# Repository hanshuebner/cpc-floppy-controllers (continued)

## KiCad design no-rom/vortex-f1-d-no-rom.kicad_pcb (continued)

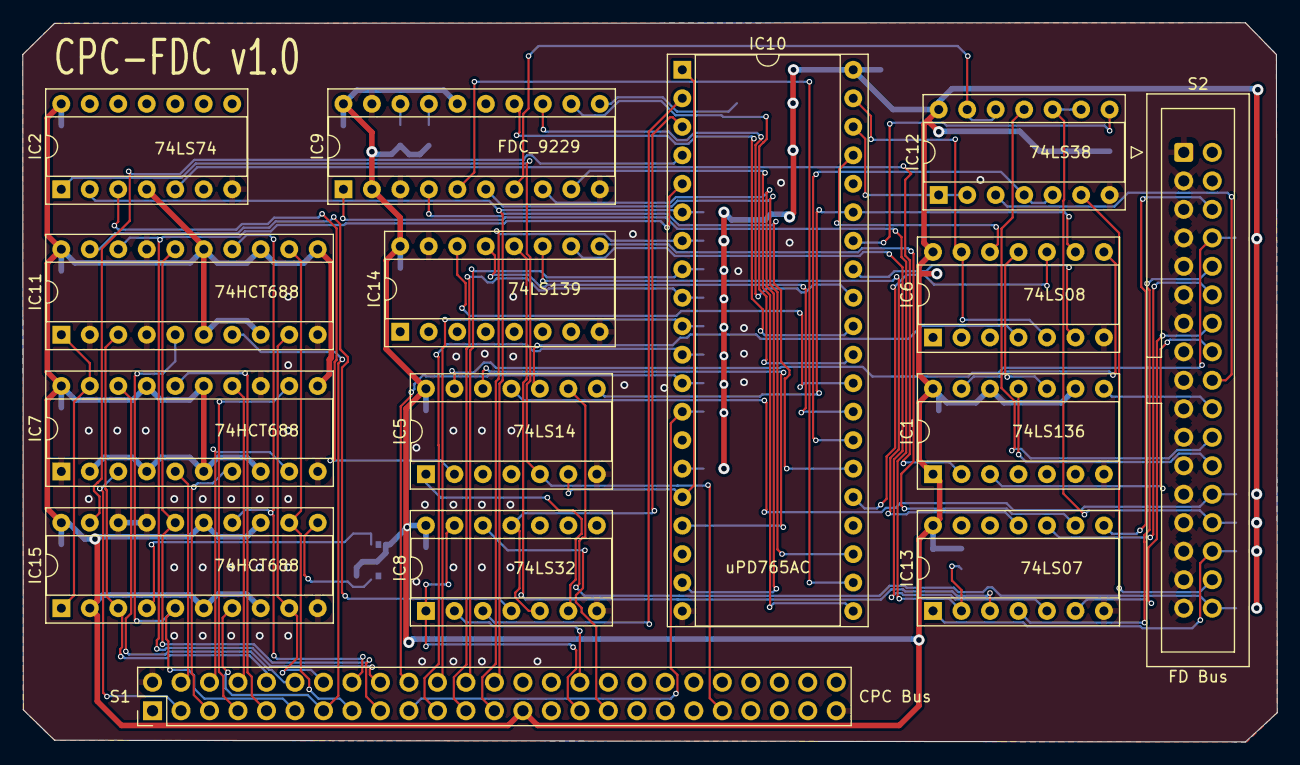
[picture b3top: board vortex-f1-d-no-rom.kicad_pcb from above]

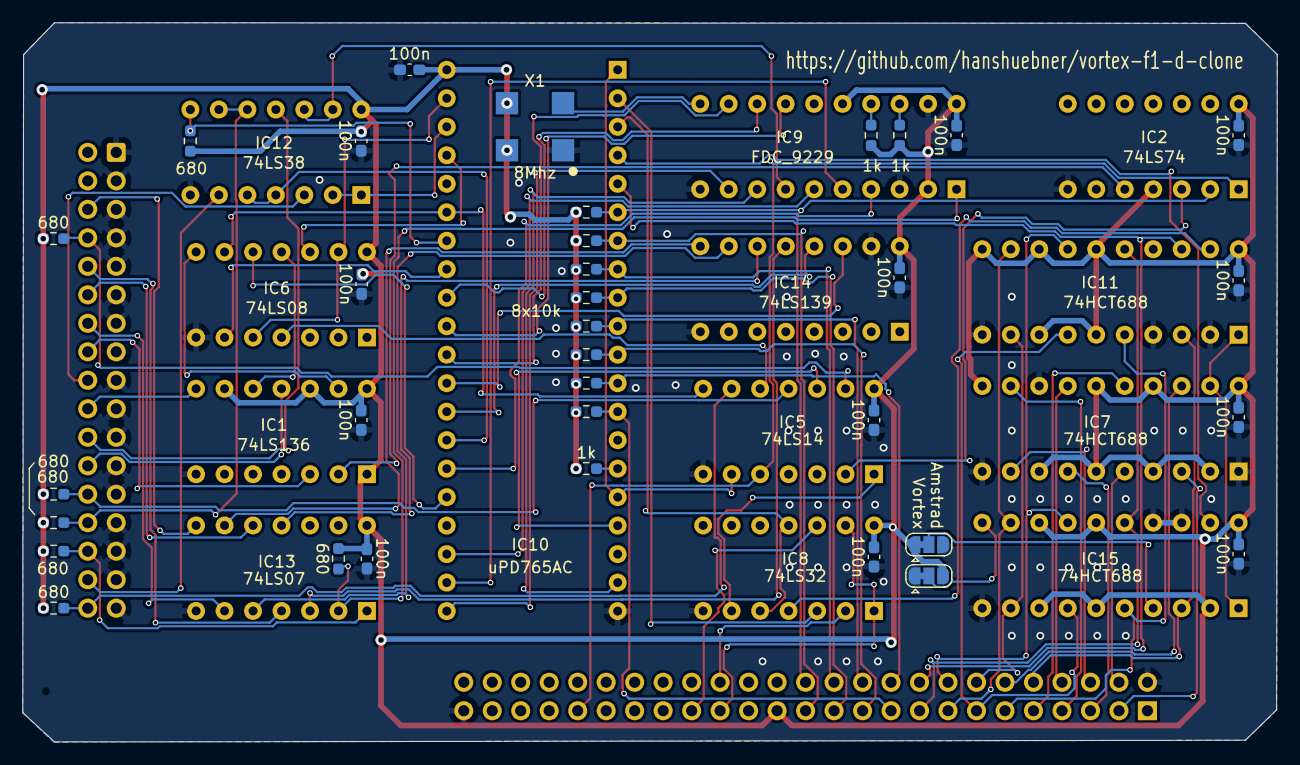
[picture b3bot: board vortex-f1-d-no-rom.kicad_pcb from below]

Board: 2 copper layers, 111.9 x 64.1 mm, 49 parts (34 on the bottom side), 88 nets.

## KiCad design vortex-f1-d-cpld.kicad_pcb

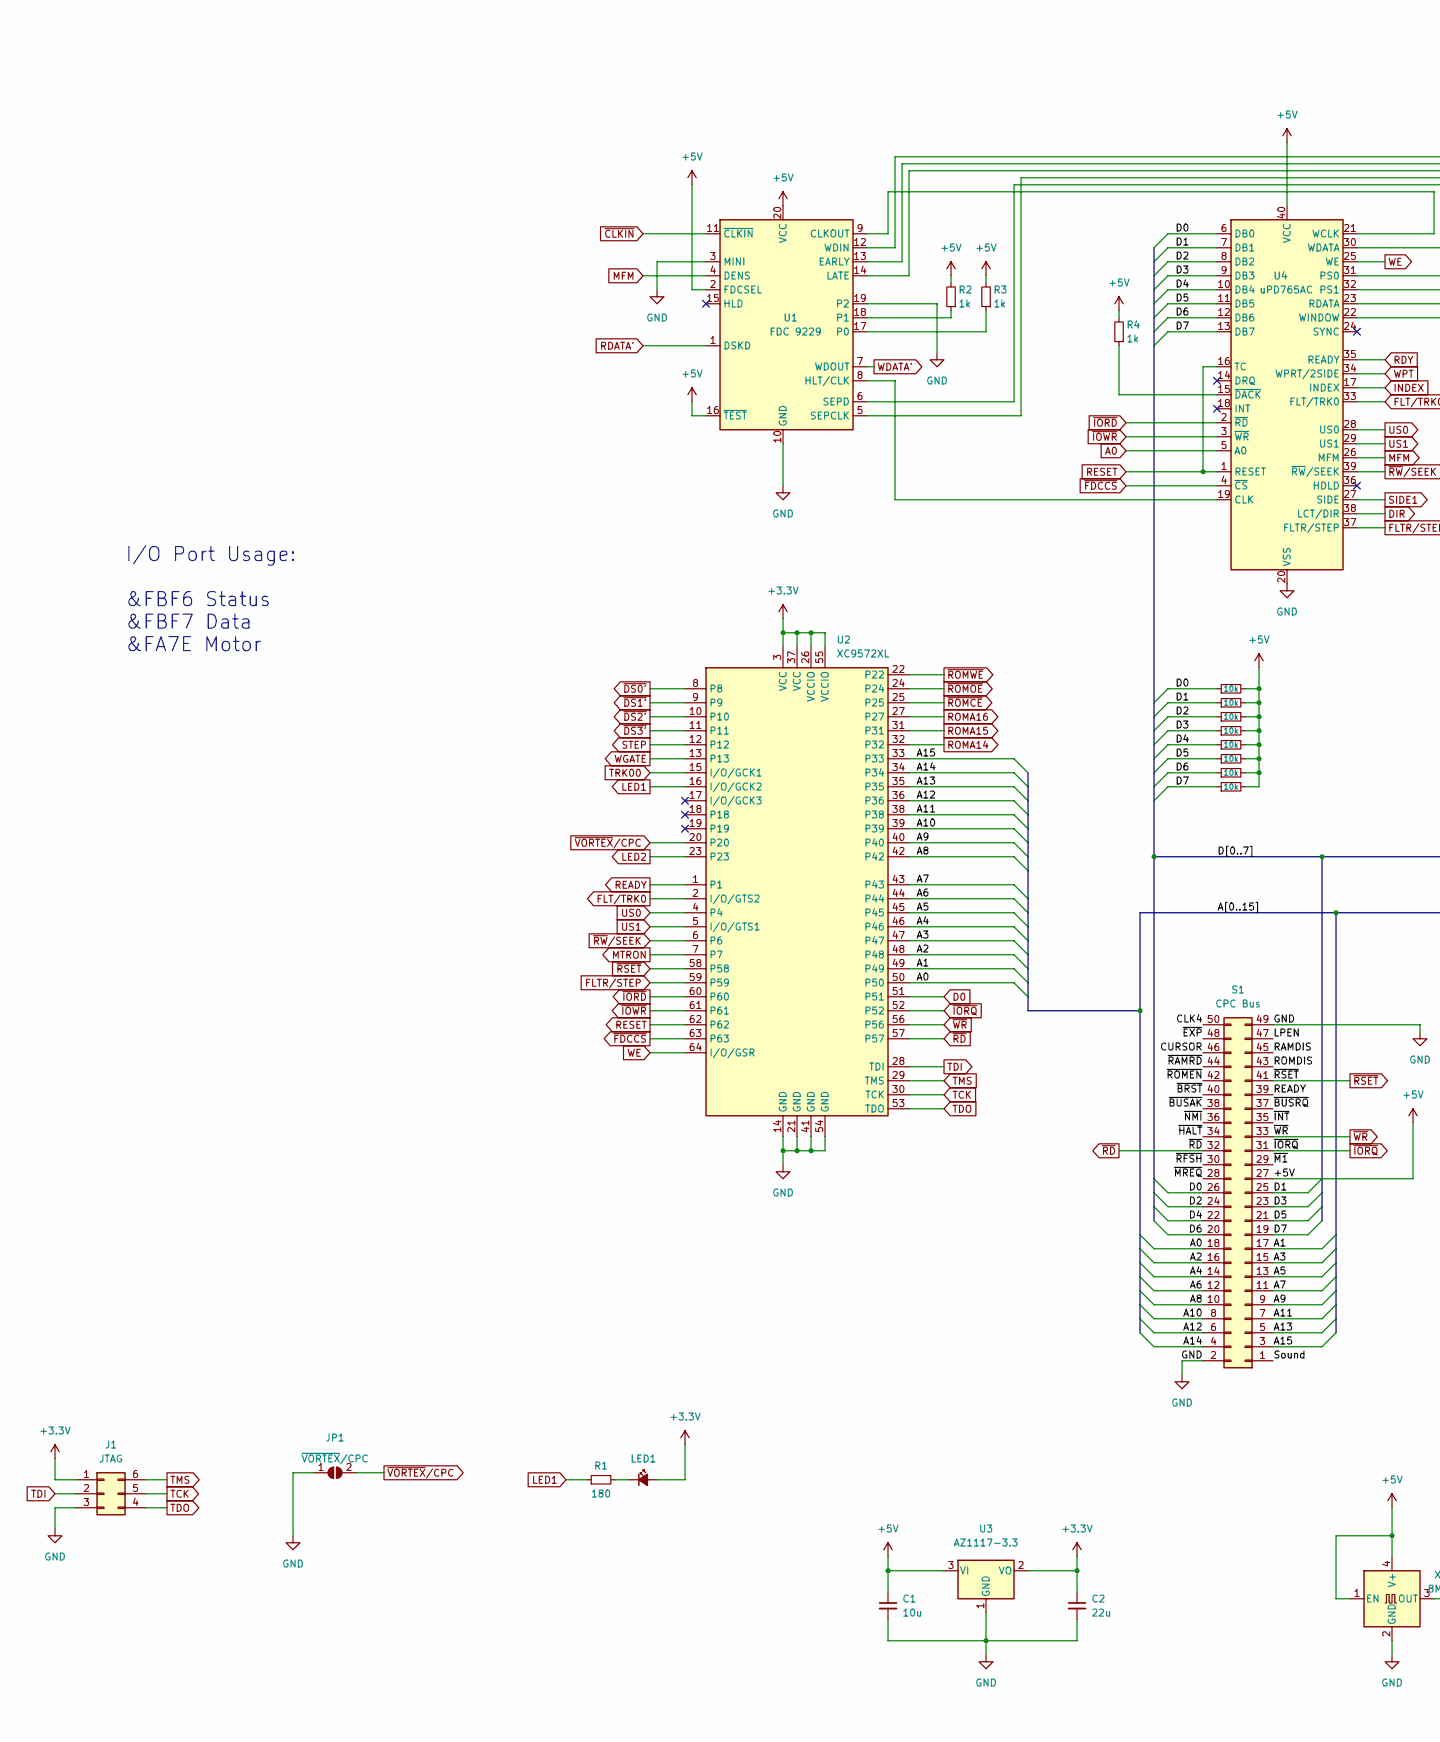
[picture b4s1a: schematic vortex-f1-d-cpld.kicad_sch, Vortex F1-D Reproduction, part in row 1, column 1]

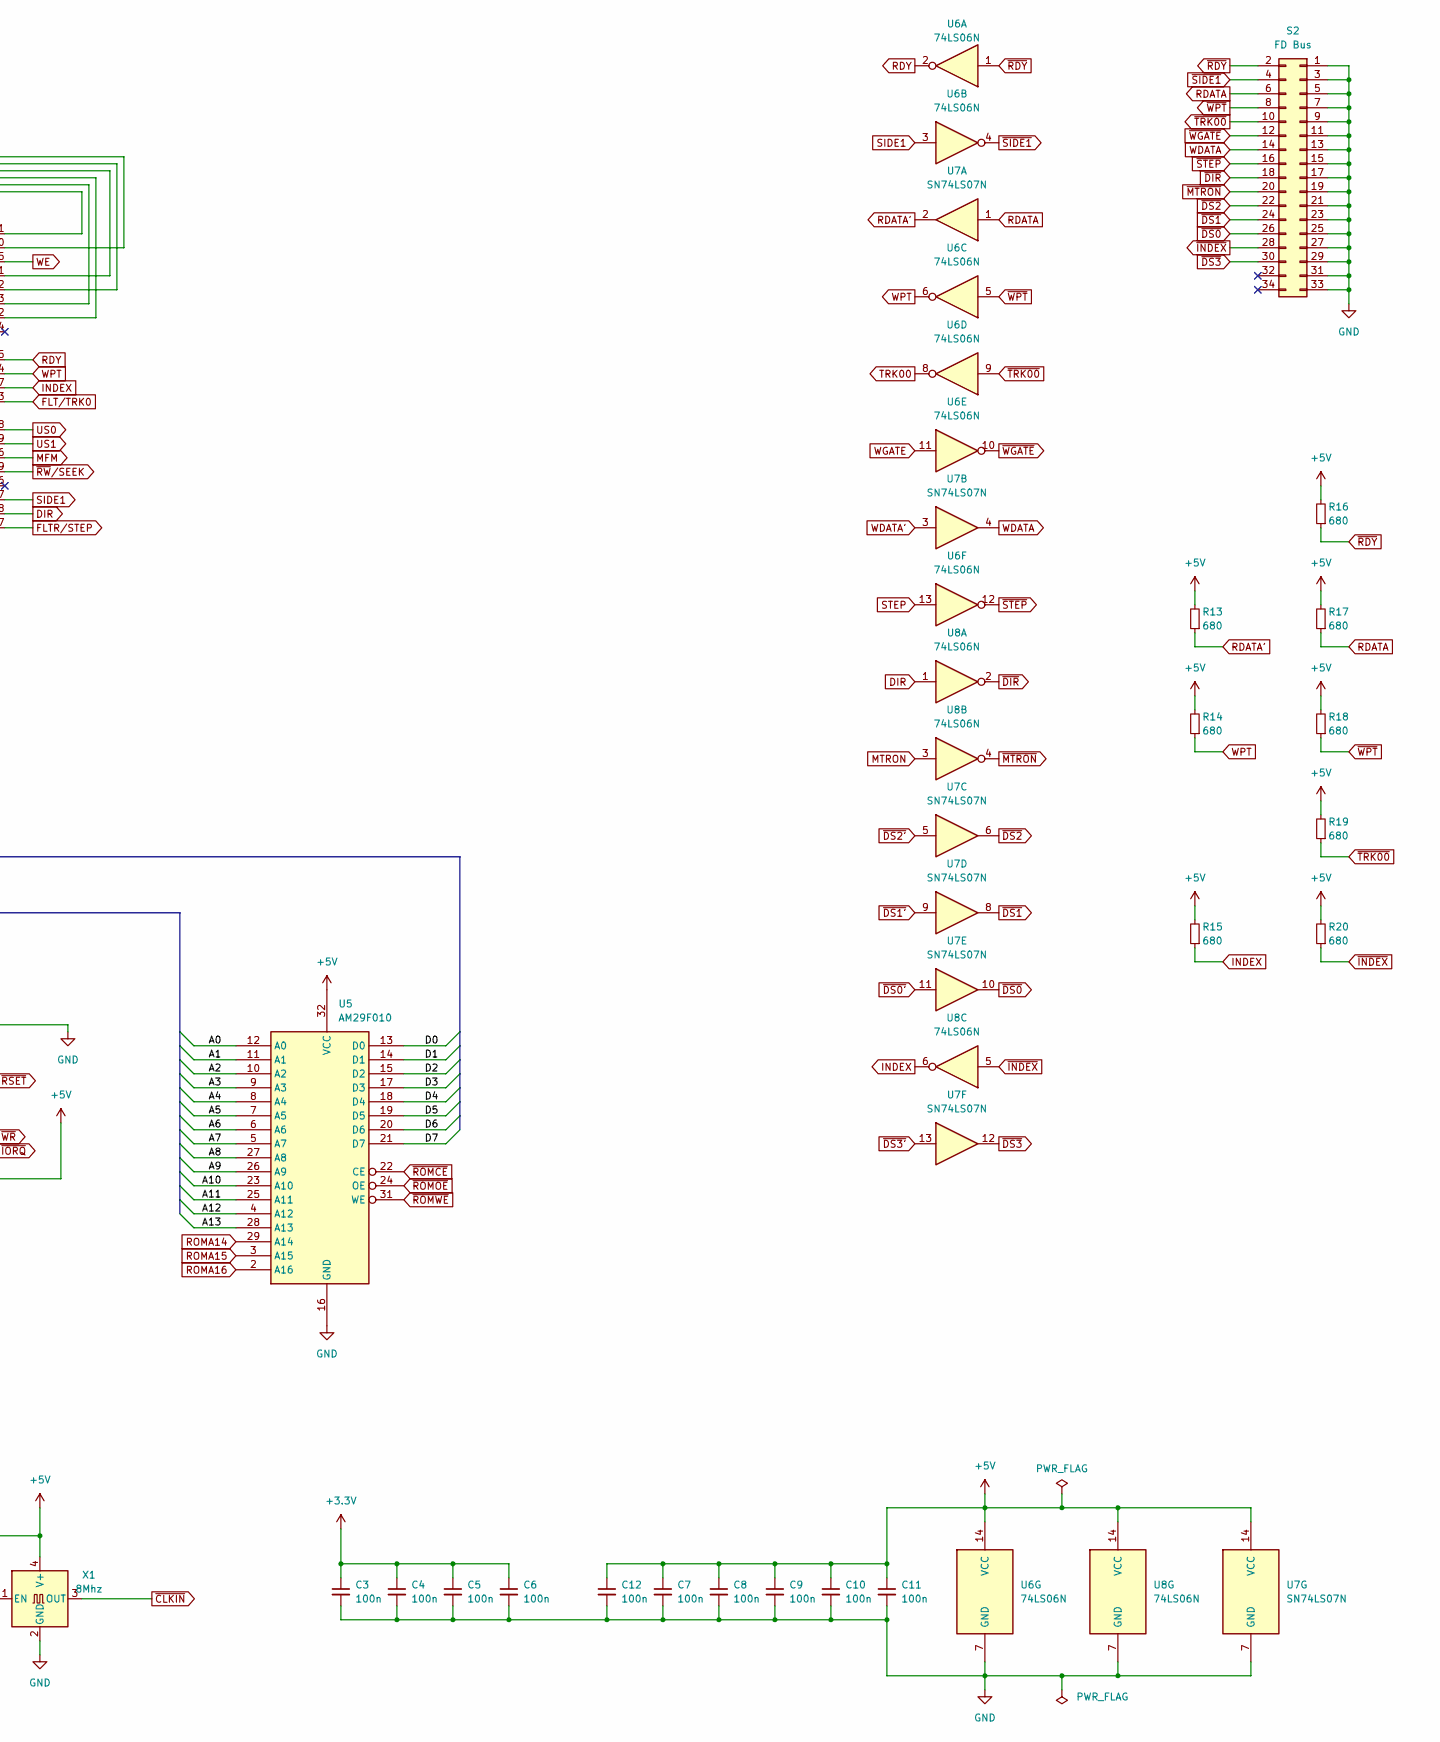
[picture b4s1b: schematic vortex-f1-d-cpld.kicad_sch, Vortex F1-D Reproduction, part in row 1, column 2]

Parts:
C1: 10u; C_0603_1608Metric_Pad1.08x0.95mm_HandSolder
C2: 22u; C_0603_1608Metric_Pad1.08x0.95mm_HandSolder
C3, C4, C5, C6, C7, C8, C9, C10, C11, C12: 100n; C_0603_1608Metric_Pad1.08x0.95mm_HandSolder
J1: JTAG; PinHeader_2x03_P2.54mm_Vertical
JP1: ~{VORTEX}/CPC; SolderJumper-2_P1.3mm_Open_RoundedPad1.0x1.5mm
LED1: STATUS; LED_0805_2012Metric_Pad1.15x1.40mm_HandSolder
R1: 180; R_0603_1608Metric_Pad0.98x0.95mm_HandSolder
R2, R3, R4: 1k; R_0603_1608Metric_Pad0.98x0.95mm_HandSolder
R5, R6, R7, R8, R9, R10, R11, R12: 10k; R_0603_1608Metric_Pad0.98x0.95mm_HandSolder
R13, R14, R15, R16, R17, R18, R19, R20: 680; R_0603_1608Metric_Pad0.98x0.95mm_HandSolder
S1: CPC Bus; IDC-Header_2x25_P2.54mm_Horizontal
S2: FD Bus; IDC-Header_2x17_P2.54mm_Horizontal
U1: FDC 9229; DIP-20_W7.62mm_Socket
U2: XC9572XL; TQFP-64_10x10mm_P0.5mm
U3: AZ1117-3.3; SOT-223-3_TabPin2
U4: uPD765AC; DIP-40_W15.24mm_Socket
U5: AM29F010; PLCC-32_THT-Socket
U6, U8: 74LS06N; SSOP-14_5.3x6.2mm_P0.65mm
U7: SN74LS07N; SSOP-14_5.3x6.2mm_P0.65mm
X1: 8Mhz; Oscillator_SMD_EuroQuartz_XO91-4Pin_7.0x5.0mm

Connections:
+3.3V: C2.1, C3.1, C4.1, C5.1, C6.1, J1.1, LED1.2 (A), U2.3 (VCC), U2.26 (VCCIO), U2.37 (VCC), U2.55 (VCCIO), U3.2 (VO)
+5V: C1.1, C7.1, C8.1, C9.1, C10.1, C11.1, C12.1, R2.2, R3.2, R4.2, R5.2, R6.2, R7.2, R8.2, R9.2, R10.2, R11.2, R12.2, R13.2, R14.2, R15.2, R16.2, R17.2, R18.2, R19.2, R20.2, S1.27, U1.2 (FDCSEL), U1.16 (~TEST), U1.20 (VCC), U3.3 (VI), U4.40 (VCC), U5.32 (VCC), U6.14 (VCC), U7.14 (VCC), U8.14 (VCC), X1.1 (EN), X1.4 (V+)
/A1: S1.17, U2.49, U5.11 (A1)
/A2: S1.16, U2.48, U5.10 (A2)
/A3: S1.15, U2.47, U5.9 (A3)
/A4: S1.14, U2.46, U5.8 (A4)
/A5: S1.13, U2.45, U5.7 (A5)
/A6: S1.12, U2.44, U5.6 (A6)
/A7: S1.11, U2.43, U5.5 (A7)
/A8: S1.10, U2.42, U5.27 (A8)
/A9: S1.9, U2.40, U5.26 (A9)
/A10: S1.8, U2.39, U5.23 (A10)
/A11: S1.7, U2.38, U5.25 (A11)
/A12: S1.6, U2.36, U5.4 (A12)
/A13: S1.5, U2.35, U5.28 (A13)
/A14: S1.4, U2.34
/A15: S1.3, U2.33
/CLK4: S1.50
/CURSOR: S1.46
/D1: R6.1, S1.25, U4.7 (DB1), U5.14 (D1)
/D2: R7.1, S1.24, U4.8 (DB2), U5.15 (D2)
/D3: R8.1, S1.23, U4.9 (DB3), U5.17 (D3)
/D4: R9.1, S1.22, U4.10 (DB4), U5.18 (D4)
/D5: R10.1, S1.21, U4.11 (DB5), U5.19 (D5)
/D6: R11.1, S1.20, U4.12 (DB6), U5.20 (D6)
/D7: R12.1, S1.19, U4.13 (DB7), U5.21 (D7)
/LPEN: S1.47
/RAMDIS: S1.45
/ROMDIS: S1.43
/Sound: S1.1
/~BRST: S1.40
/~BUSAK: S1.38
/~BUSRQ: S1.37
/~EXP: S1.48
/~HALT: S1.34
/~INT: S1.35
/~M1: S1.29
/~MREQ: S1.28
/~NMI: S1.36
/~RAMRD: S1.44
/~RFSH: S1.30
/~ROMEN: S1.42
A0: S1.18, U2.50, U4.5 (A0), U5.12 (A0)
D0: R5.1, S1.26, U2.51, U4.6 (DB0), U5.13 (D0)
DIR: U4.38 (LCT/DIR), U8.1
FLTR/STEP: U2.59, U4.37 (FLTR/STEP)
FLT/TRK0: U2.2 (I/O/GTS2), U4.33 (FLT/TRK0)
GND: C1.2, C2.2, C3.2, C4.2, C5.2, C6.2, C7.2, C8.2, C9.2, C10.2, C11.2, C12.2, J1.3, JP1.1 (A), S1.2, S1.49, S2.1, S2.3, S2.5, S2.7, S2.9, S2.11, S2.13, S2.15, S2.17, S2.19, S2.21, S2.23, S2.25, S2.27, S2.29, S2.31, S2.33, U1.3 (MINI), U1.10 (GND), U1.19 (P2), U2.14 (GND), U2.21 (GND), U2.41 (GND), U2.54 (GND), U3.1 (GND), U4.20 (VSS), U5.16 (GND), U6.7 (GND), U7.7 (GND), U8.7 (GND), X1.2 (GND)
INDEX: R15.1, U4.17 (INDEX), U8.6
LED1: R1.1, U2.16 (I/O/GCK2)
LED2: U2.23
MFM: U1.4 (DENS), U4.26 (MFM)
MTRON: U2.7, U8.3
unnamed: LED1.1 (K), R1.2
unnamed: R2.1, U1.18 (P1)
unnamed: R3.1, U1.17 (P0)
unnamed: R4.1, U4.15 (~DACK)
unnamed: U1.5 (SEPCLK), U4.22 (WINDOW)
unnamed: U1.6 (SEPD), U4.23 (RDATA)
unnamed: U1.8 (HLT/CLK), U4.19 (CLK)
unnamed: U1.9 (CLKOUT), U4.21 (WCLK)
unnamed: U1.12 (WDIN), U4.30 (WDATA)
unnamed: U1.13 (EARLY), U4.32 (PS1)
unnamed: U1.14 (LATE), U4.31 (PS0)
RDATA: R17.1, S2.6, U7.1
RDATA': R13.1, U1.1 (DSKD), U7.2
RDY: U4.35 (READY), U6.2
READY: S1.39, U2.1
RESET: U2.62, U4.1 (RESET), U4.16 (TC)
ROMA14: U2.32, U5.29 (A14)
ROMA15: U2.31, U5.3 (A15)
ROMA16: U2.27, U5.2 (A16)
SIDE1: U4.27 (SIDE), U6.3
STEP: U2.12, U6.13
TCK: J1.5, U2.30 (TCK)
TDI: J1.2, U2.28 (TDI)
TDO: J1.4, U2.53 (TDO)
TMS: J1.6, U2.29 (TMS)
TRK00: U2.15 (I/O/GCK1), U6.8
US0: U2.4, U4.28 (US0)
US1: U2.5 (I/O/GTS1), U4.29 (US1)
WDATA: S2.14, U7.4
WDATA': U1.7 (WDOUT), U7.3
WE: U2.64 (I/O/GSR), U4.25 (WE)
WGATE: U2.13, U6.11
WPT: R14.1, U4.34 (WPRT/2SIDE), U6.6
~CLKIN: U1.11 (~CLKIN), X1.3 (OUT)
~DIR: S2.18, U8.2
~DS0': U2.8, U7.11
~DS0: S2.26, U7.10
~DS1': U2.9, U7.9
~DS1: S2.24, U7.8
~DS2': U2.10, U7.5
~DS2: S2.22, U7.6
~DS3': U2.11, U7.13
~DS3: S2.30, U7.12
~FDCCS: U2.63, U4.4 (~CS)
~INDEX: R20.1, S2.28, U8.5
~IORD: U2.60, U4.2 (~RD)
~IORQ: S1.31, U2.52
~IOWR: U2.61, U4.3 (~WR)
~MTRON: S2.20, U8.4
~RDY: R16.1, S2.2, U6.1
~RD: S1.32, U2.57
~ROMCE: U2.25, U5.22 (CE)
~ROMOE: U2.24, U5.24 (OE)
~ROMWE: U2.22, U5.31 (WE)
~RSET: S1.41, U2.58
~RW/SEEK: U2.6, U4.39 (~RW/SEEK)
~SIDE1: S2.4, U6.4
~STEP: S2.16, U6.12
~TRK00: R19.1, S2.10, U6.9
~VORTEX/CPC: JP1.2 (B), U2.20
~WGATE: S2.12, U6.10
~WPT: R18.1, S2.8, U6.5
~WR: S1.33, U2.56

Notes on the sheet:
I/O Port Usage: &FBF6 Status &FBF7 Data &FA7E Motor

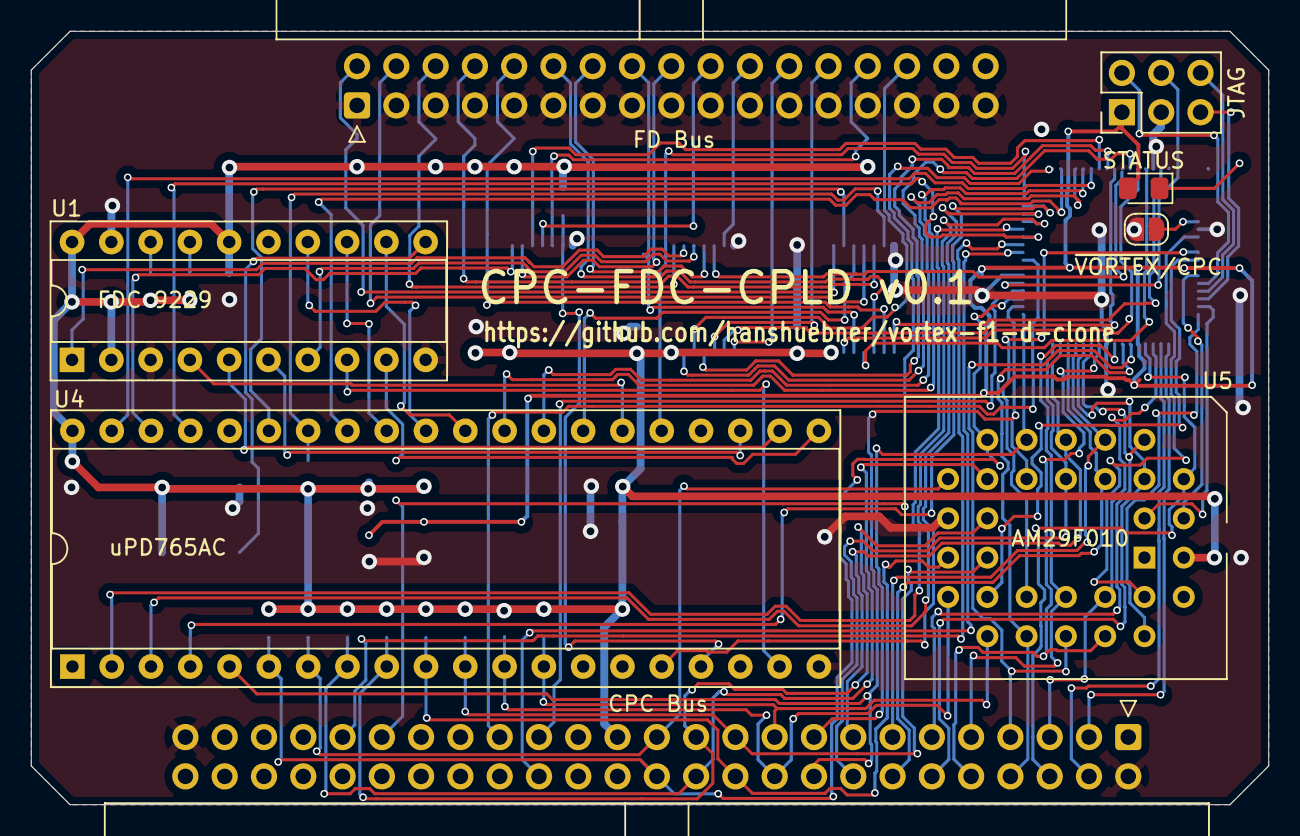
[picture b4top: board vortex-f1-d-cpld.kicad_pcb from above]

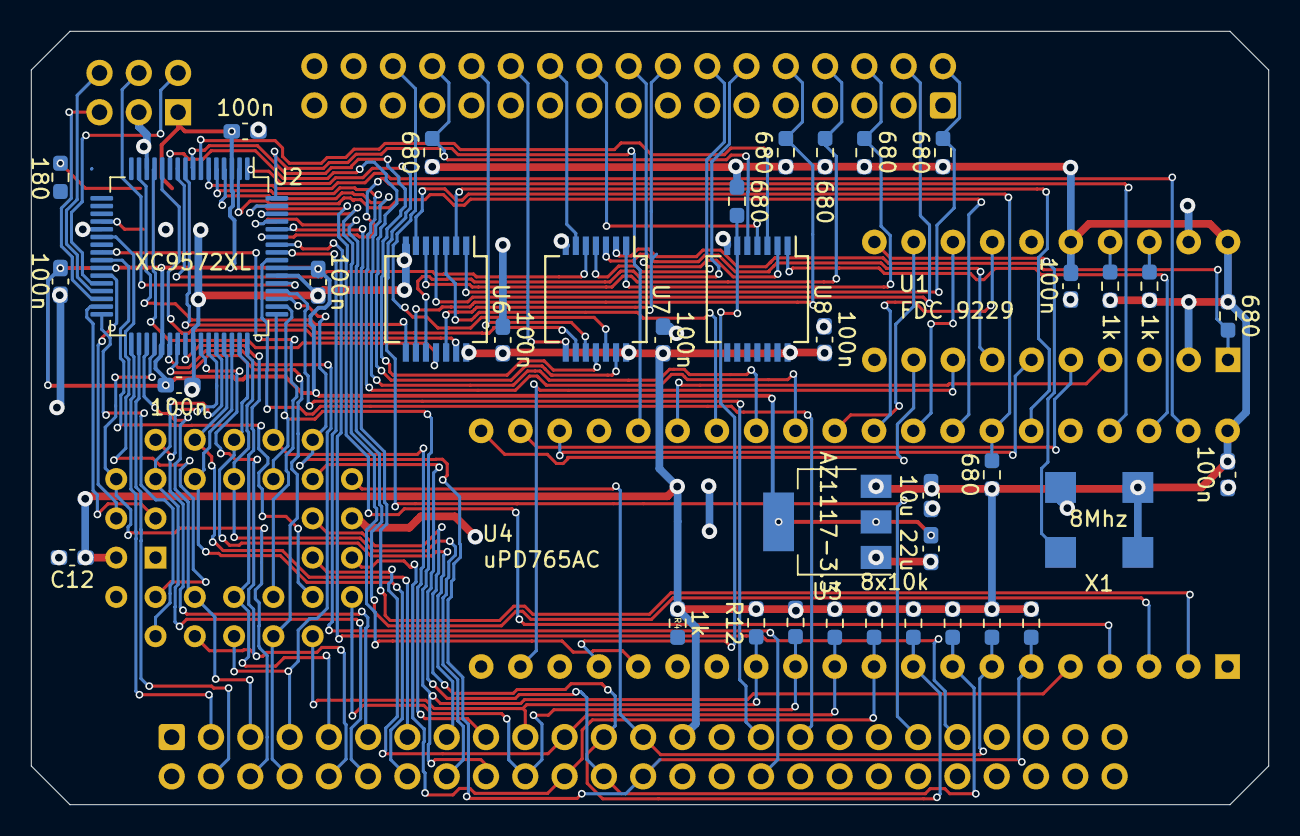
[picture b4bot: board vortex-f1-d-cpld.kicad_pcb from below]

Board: 2 copper layers, 80.0 x 50.0 mm, 46 parts (38 on the bottom side), 97 nets.

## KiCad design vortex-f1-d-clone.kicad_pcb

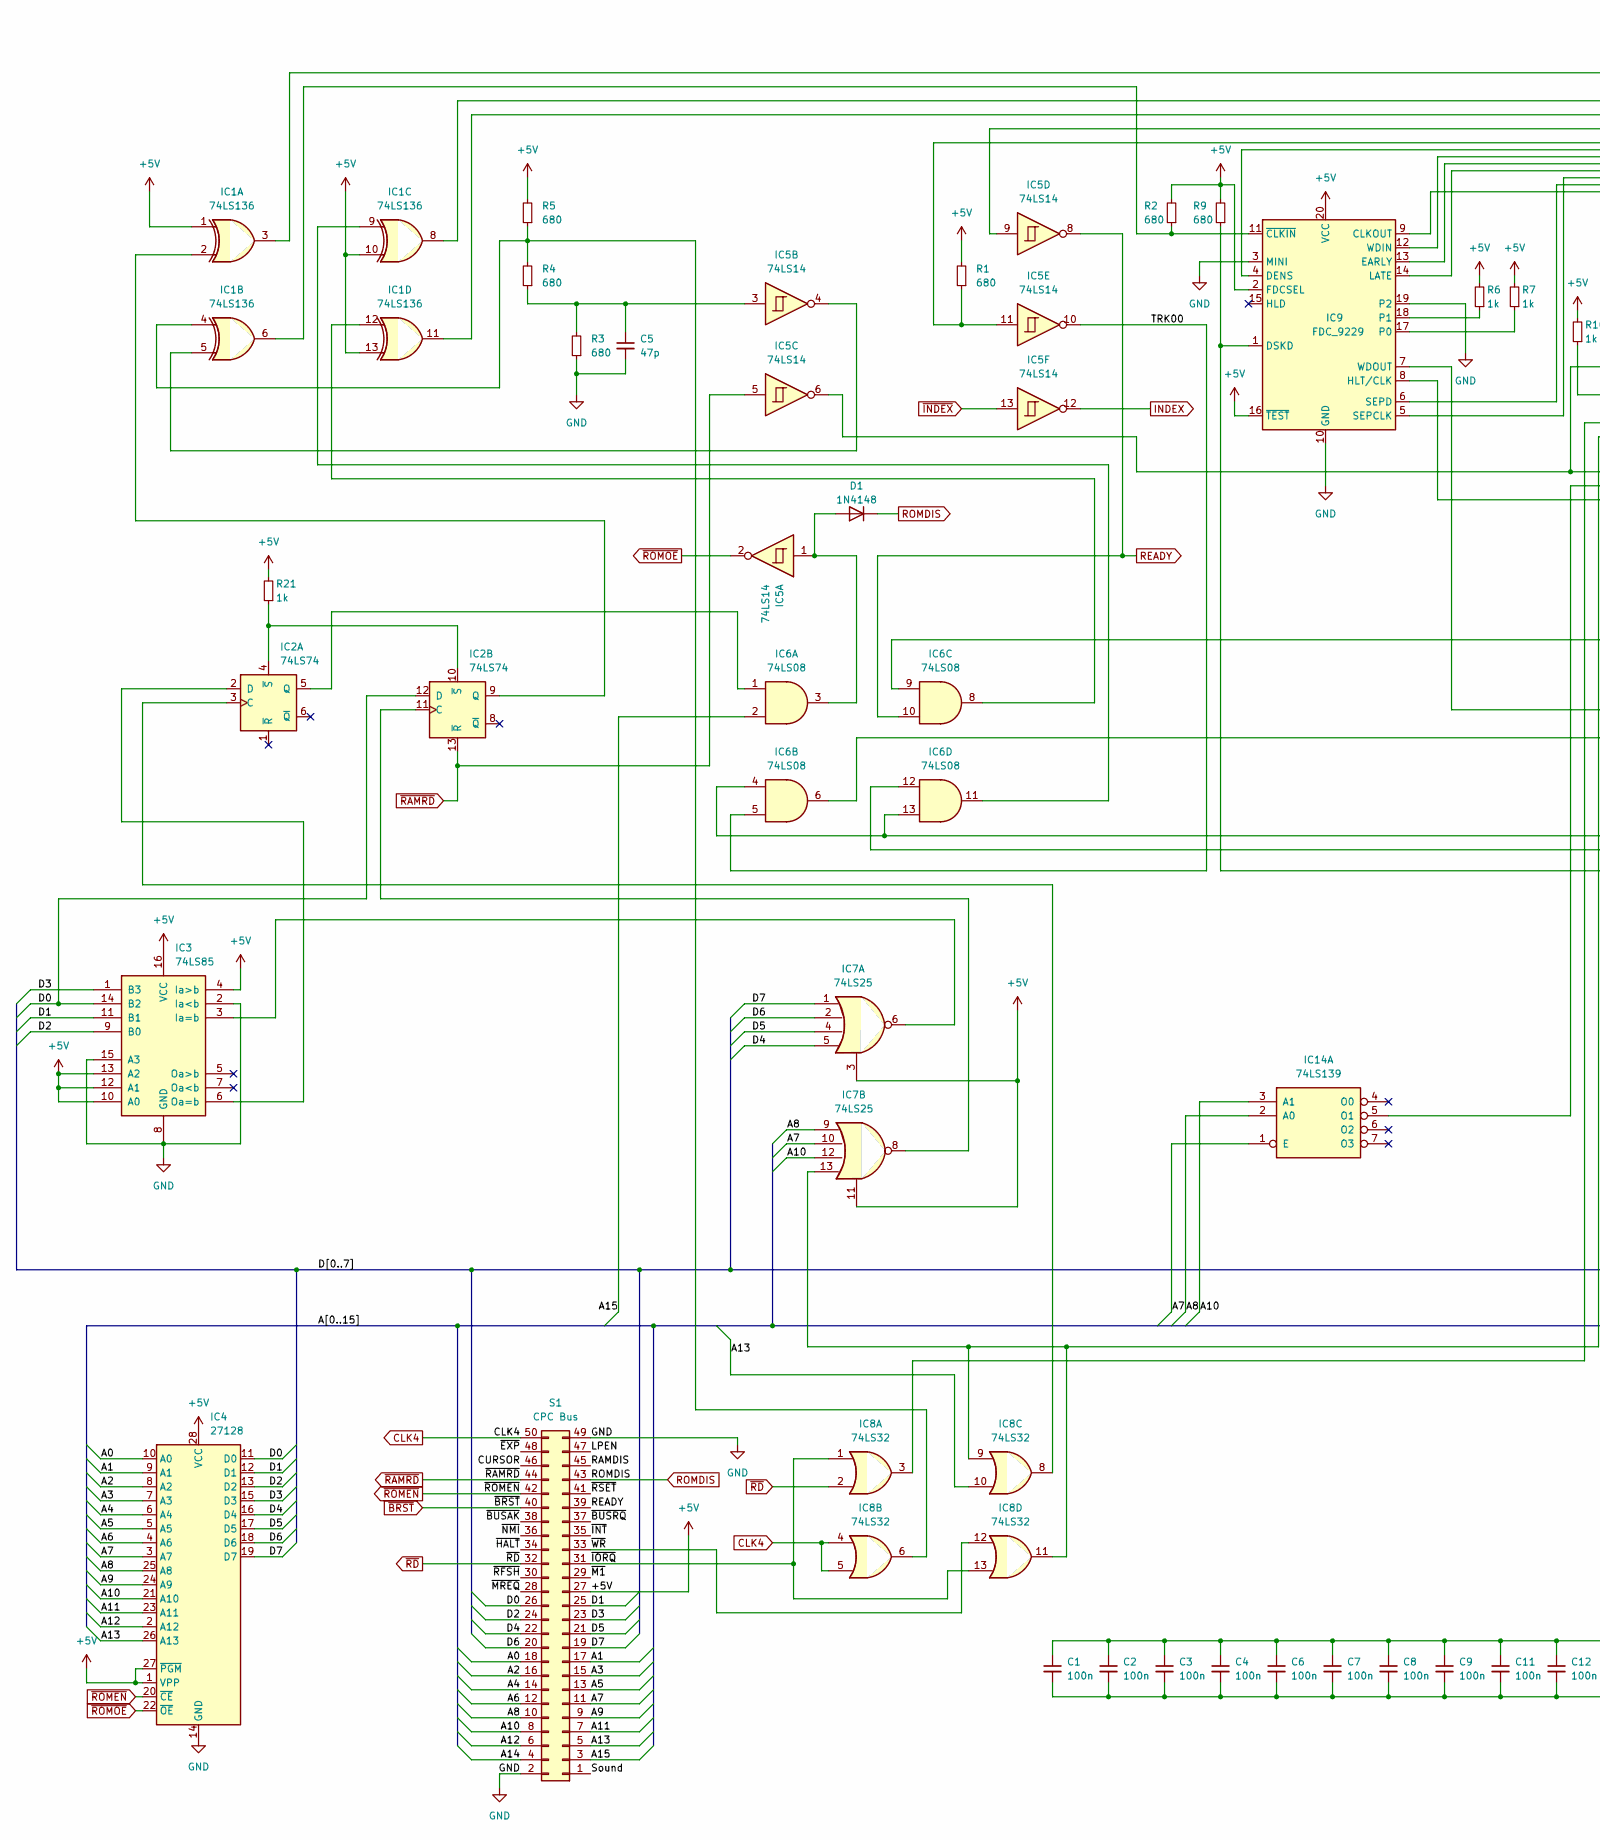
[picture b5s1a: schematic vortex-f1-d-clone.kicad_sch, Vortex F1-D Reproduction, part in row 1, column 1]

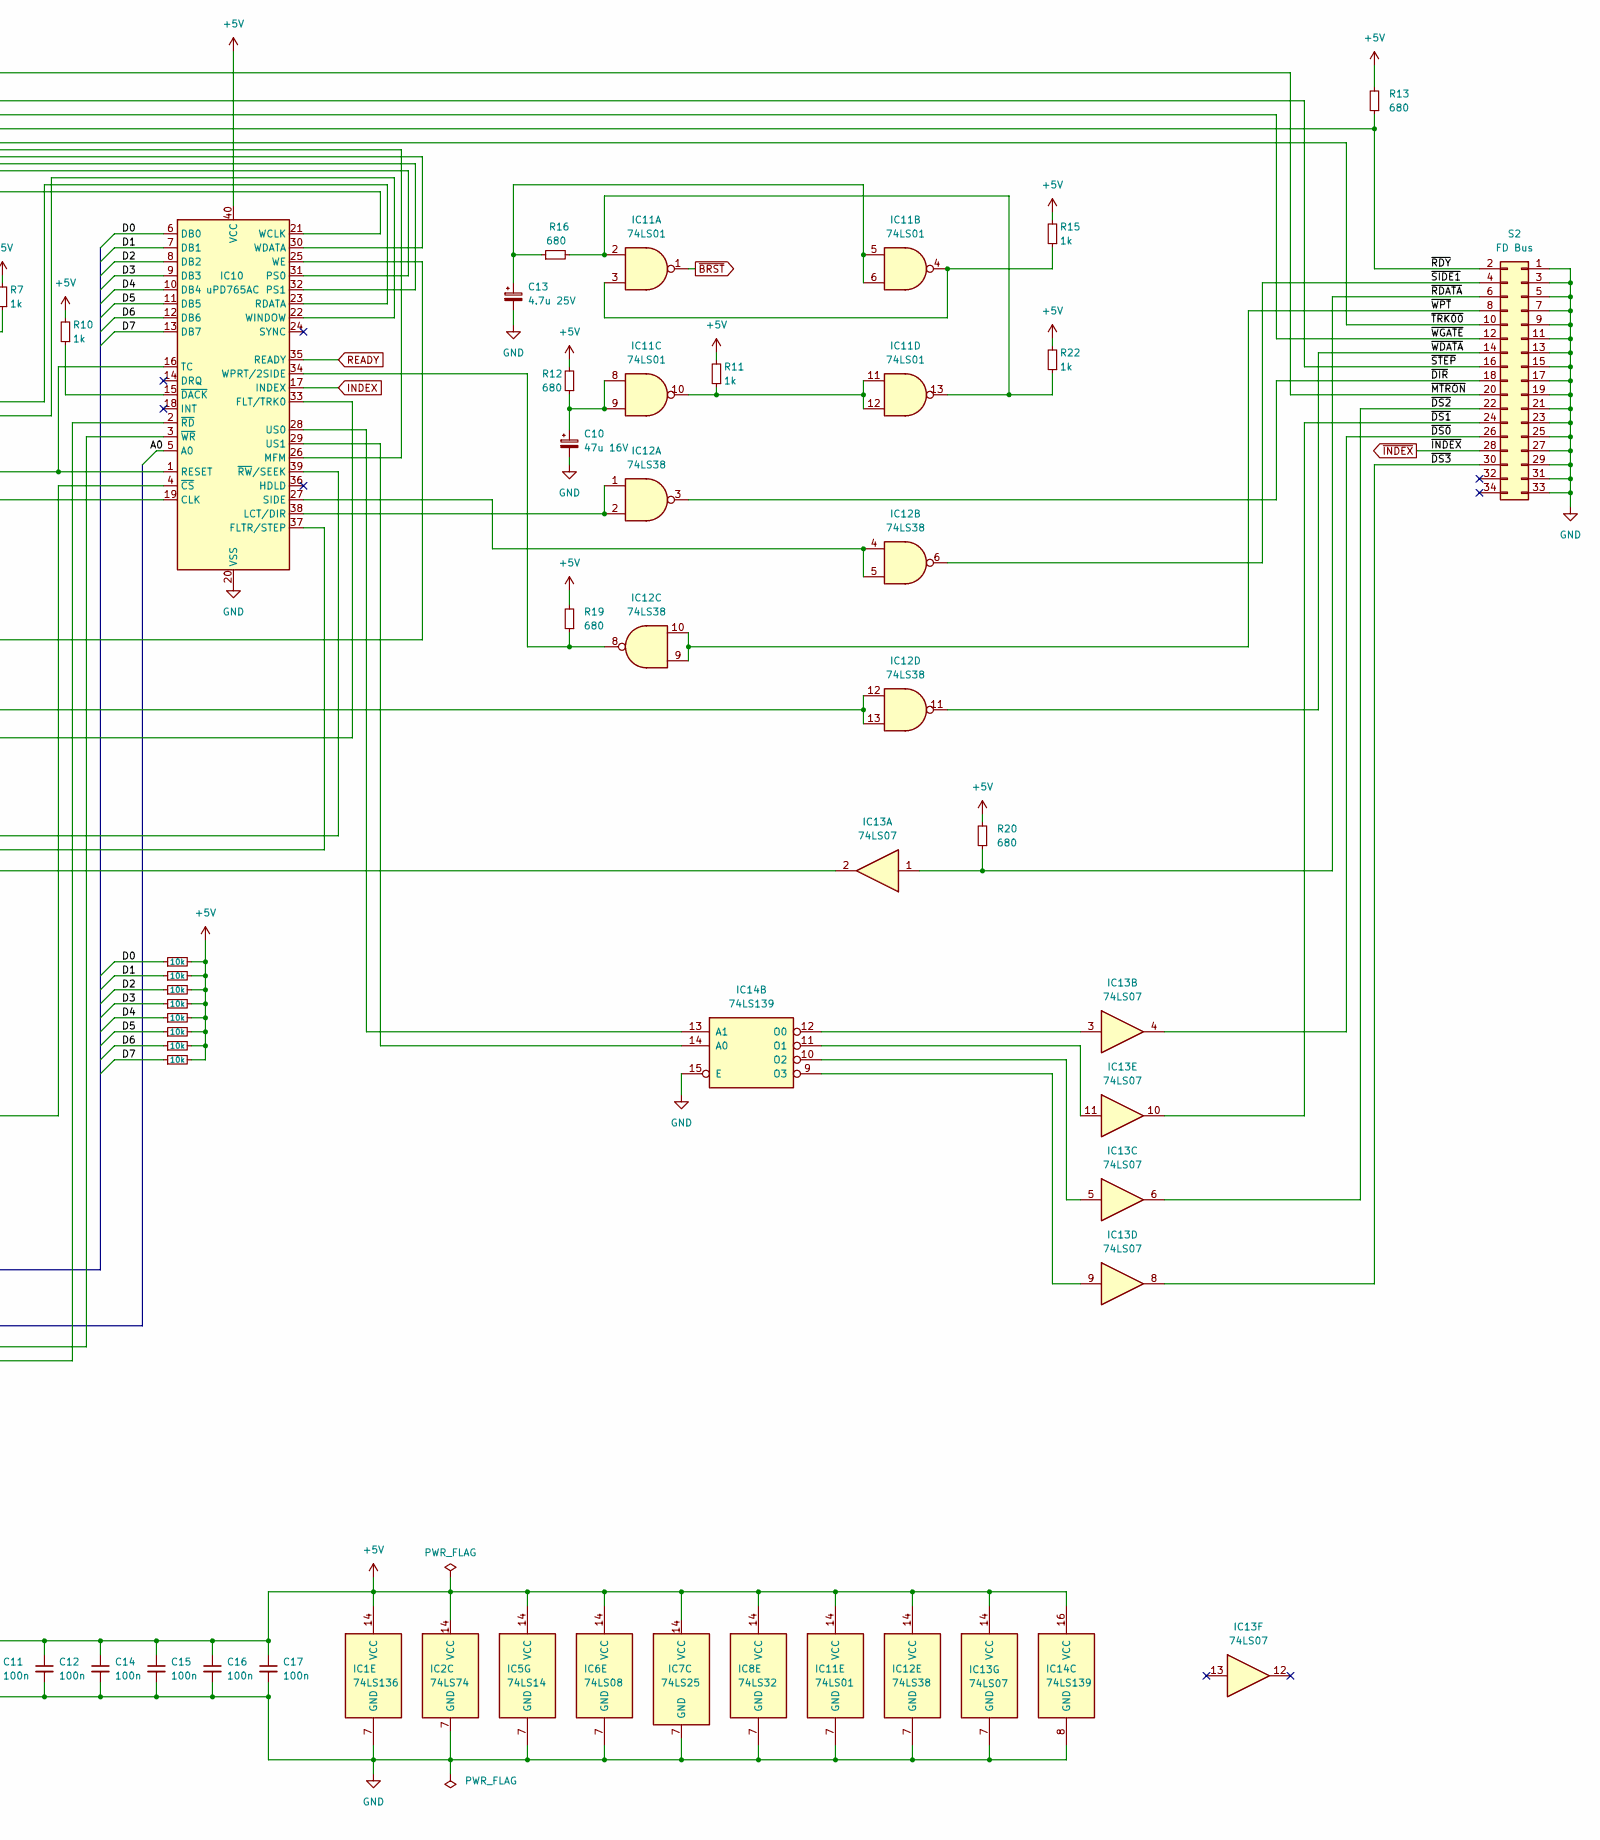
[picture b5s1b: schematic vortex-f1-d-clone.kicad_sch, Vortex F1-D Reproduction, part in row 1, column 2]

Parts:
C1, C2, C3, C4, C6, C7, C8, C9, C11, C12, C14, C15, C16, C17: 100n; C_0603_1608Metric_Pad1.08x0.95mm_HandSolder
C5: 47p; C_0603_1608Metric_Pad1.08x0.95mm_HandSolder
C10: 47u 16V; C_0805_2012Metric_Pad1.18x1.45mm_HandSolder
C13: 4.7u 25V; C_0805_2012Metric_Pad1.18x1.45mm_HandSolder
D1: 1N4148; D_DO-35_SOD27_P7.62mm_Horizontal
IC1: 74LS136; DIP-14_W7.62mm_Socket
IC2: 74LS74; DIP-14_W7.62mm_Socket
IC3: 74LS85; DIP-16_W7.62mm_Socket
IC4: 27128; DIP-28_W15.24mm
IC5: 74LS14; DIP-14_W7.62mm_Socket
IC6: 74LS08; DIP-14_W7.62mm_Socket
IC7: 74LS25; DIP-14_W7.62mm_Socket
IC8: 74LS32; DIP-14_W7.62mm_Socket
IC9: FDC_9229; DIP-20_W7.62mm_Socket
IC10: uPD765AC; DIP-40_W15.24mm_Socket
IC11: 74LS01; DIP-14_W7.62mm_Socket
IC12: 74LS38; DIP-14_W7.62mm_Socket
IC13: 74LS07; DIP-14_W7.62mm_Socket
IC14: 74LS139; DIP-16_W7.62mm_Socket
R1, R2, R3, R4, R5, R9, R12, R13, R16, R19, R20: 680; R_0603_1608Metric_Pad0.98x0.95mm_HandSolder
R6, R7, R10, R11, R15, R21, R22: 1k; R_0603_1608Metric_Pad0.98x0.95mm_HandSolder
R8, R14, R17, R18, R23, R24, R25, R26: 10k; R_0603_1608Metric_Pad0.98x0.95mm_HandSolder
S1: CPC Bus; PinHeader_2x25_P2.54mm_Vertical
S2: FD Bus; IDC-Header_2x17_P2.54mm_Vertical

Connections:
+5V: C1.1, C2.1, C3.1, C4.1, C6.1, C7.1, C8.1, C9.1, C11.1, C12.1, C14.1, C15.1, C16.1, C17.1, IC1.1, IC1.10, IC1.13, IC1.14 (VCC), IC2.14 (VCC), IC3.4 (Ia>b), IC3.10 (A0), IC3.12 (A1), IC3.13 (A2), IC3.16 (VCC), IC4.1 (VPP), IC4.27 (~PGM), IC4.28 (VCC), IC5.14 (VCC), IC6.14 (VCC), IC7.3, IC7.11, IC7.14 (VCC), IC8.14 (VCC), IC9.2 (FDCSEL), IC9.16 (~TEST), IC9.20 (VCC), IC10.40 (VCC), IC11.14 (VCC), IC12.14 (VCC), IC13.14 (VCC), IC14.16 (VCC), R1.2, R2.2, R5.2, R6.2, R7.2, R8.2, R9.2, R10.2, R11.2, R12.2, R13.2, R14.2, R15.2, R17.2, R18.2, R19.2, R20.2, R21.2, R22.2, R23.2, R24.2, R25.2, R26.2, S1.27
/A0: IC4.10 (A0), IC10.5 (A0), S1.18
/A1: IC4.9 (A1), S1.17
/A2: IC4.8 (A2), S1.16
/A3: IC4.7 (A3), S1.15
/A4: IC4.6 (A4), S1.14
/A5: IC4.5 (A5), S1.13
/A6: IC4.4 (A6), S1.12
/A7: IC4.3 (A7), IC7.10, IC14.1 (E), S1.11
/A8: IC4.25 (A8), IC7.9, IC14.2 (A0), S1.10
/A9: IC4.24 (A9), S1.9
/A10: IC4.21 (A10), IC7.12, IC14.3 (A1), S1.8
/A11: IC4.23 (A11), S1.7
/A12: IC4.2 (A12), S1.6
/A13: IC4.26 (A13), IC8.10, S1.5
/A14: S1.4
/A15: IC6.2, S1.3
/CURSOR: S1.46
/D0: IC2.12 (D), IC3.14 (B2), IC4.11 (D0), IC10.6 (DB0), R8.1, S1.26
/D1: IC3.11 (B1), IC4.12 (D1), IC10.7 (DB1), R14.1, S1.25
/D2: IC3.9 (B0), IC4.13 (D2), IC10.8 (DB2), R17.1, S1.24
/D3: IC3.1 (B3), IC4.15 (D3), IC10.9 (DB3), R18.1, S1.23
/D4: IC4.16 (D4), IC7.5, IC10.10 (DB4), R23.1, S1.22
/D5: IC4.17 (D5), IC7.4, IC10.11 (DB5), R24.1, S1.21
/D6: IC4.18 (D6), IC7.2, IC10.12 (DB6), R25.1, S1.20
/D7: IC4.19 (D7), IC7.1, IC10.13 (DB7), R26.1, S1.19
/LPEN: S1.47
/RAMDIS: S1.45
/Sound: S1.1
/TRK00: IC5.10, IC6.5
/~BUSAK: S1.38
/~BUSRQ: S1.37
/~DIR: IC12.3, S2.18
/~DS0: IC13.4, S2.26
/~DS1: IC13.10, S2.24
/~DS2: IC13.6, S2.22
/~DS3: IC13.8, S2.30
/~EXP: S1.48
/~HALT: S1.34
/~INT: S1.35
/~IORQ: IC8.1, IC8.13, S1.31
/~M1: S1.29
/~MREQ: S1.28
/~MTRON: IC1.3, S2.20
/~NMI: S1.36
/~RDATA: IC13.1, R20.1, S2.6
/~RDY: IC5.9, R13.1, S2.2
/~RFSH: S1.30
/~RSET: S1.41
/~SIDE1: IC12.6, S2.4
/~STEP: IC1.8, S2.16
/~TRK00: IC5.11, R1.1, S2.10
/~WDATA: IC12.11, S2.14
/~WGATE: IC1.11, S2.12
/~WPT: IC12.9, IC12.10, S2.8
/~WR: IC8.12, S1.33
CLK4: IC8.4, IC8.5, S1.50
GND: C1.2, C2.2, C3.2, C4.2, C5.2, C6.2, C7.2, C8.2, C9.2, C10.2, C11.2, C12.2, C13.2, C14.2, C15.2, C16.2, C17.2, IC1.7 (GND), IC2.7 (GND), IC3.2 (Ia<b), IC3.8 (GND), IC3.15 (A3), IC4.14 (GND), IC5.7 (GND), IC6.7 (GND), IC7.7 (GND), IC8.7 (GND), IC9.3 (MINI), IC9.10 (GND), IC9.19 (P2), IC10.20 (VSS), IC11.7 (GND), IC12.7 (GND), IC13.7 (GND), IC14.8 (GND), IC14.15 (E), R3.1, S1.2, S1.49, S2.1, S2.3, S2.5, S2.7, S2.9, S2.11, S2.13, S2.15, S2.17, S2.19, S2.21, S2.23, S2.25, S2.27, S2.29, S2.31, S2.33
INDEX: IC5.12, IC10.17 (INDEX)
unnamed: C5.1, IC5.3, R3.2, R4.1
unnamed: C10.1, IC11.8, IC11.9, R12.1
unnamed: C13.1, IC11.5, IC11.6, R16.1
unnamed: D1.2 (A), IC5.1, IC6.3
unnamed: IC1.2, IC2.9 (Q)
unnamed: IC1.4, IC8.6, R4.2, R5.1
unnamed: IC1.5, IC5.4
unnamed: IC1.6, IC9.11 (~CLKIN), R2.1
unnamed: IC1.9, IC6.11
unnamed: IC1.12, IC6.8
unnamed: IC2.2 (D), IC3.6 (Oa=b)
unnamed: IC2.3 (C), IC8.8
unnamed: IC2.5 (Q), IC6.1
unnamed: IC2.4 (~S), IC2.10 (~S), R21.1
unnamed: IC2.11 (C), IC7.8
unnamed: IC3.3 (Ia=b), IC7.6
unnamed: IC5.6, IC10.1 (RESET), IC10.16 (TC)
unnamed: IC6.6, IC10.33 (FLT/TRK0)
unnamed: IC6.9, IC10.25 (WE)
unnamed: IC6.12, IC10.37 (FLTR/STEP)
unnamed: IC6.4, IC6.13, IC10.39 (~RW/SEEK)
unnamed: IC7.13, IC8.9, IC8.11, IC10.3 (~WR)
unnamed: IC8.3, IC10.2 (~RD)
unnamed: IC9.1 (DSKD), IC13.2, R9.1
unnamed: IC9.4 (DENS), IC10.26 (MFM)
unnamed: IC9.5 (SEPCLK), IC10.22 (WINDOW)
unnamed: IC9.6 (SEPD), IC10.23 (RDATA)
unnamed: IC9.7 (WDOUT), IC12.12, IC12.13
unnamed: IC9.8 (HLT/CLK), IC10.19 (CLK)
unnamed: IC9.9 (CLKOUT), IC10.21 (WCLK)
unnamed: IC9.12 (WDIN), IC10.30 (WDATA)
unnamed: IC9.13 (EARLY), IC10.32 (PS1)
unnamed: IC9.14 (LATE), IC10.31 (PS0)
unnamed: IC9.17 (P0), R7.1
unnamed: IC9.18 (P1), R6.1
unnamed: IC10.4 (~CS), IC14.5 (O1)
unnamed: IC10.15 (~DACK), R10.1
unnamed: IC10.27 (SIDE), IC12.4, IC12.5
unnamed: IC10.28 (US0), IC14.13 (A1)
unnamed: IC10.29 (US1), IC14.14 (A0)
unnamed: IC10.34 (WPRT/2SIDE), IC12.8, R19.1
unnamed: IC10.38 (LCT/DIR), IC12.1, IC12.2
unnamed: IC11.3, IC11.4, R15.1
unnamed: IC11.10, IC11.11, IC11.12, R11.1
unnamed: IC11.2, IC11.13, R16.2, R22.1
unnamed: IC13.3, IC14.12 (O0)
unnamed: IC13.5, IC14.10 (O2)
unnamed: IC13.9, IC14.9 (O3)
unnamed: IC13.11, IC14.11 (O1)
READY: IC5.8, IC6.10, IC10.35 (READY), S1.39
ROMDIS: D1.1 (K), S1.43
~BRST: IC11.1, S1.40
~INDEX: IC5.13, S2.28
~RAMRD: IC2.13 (~R), IC5.5, S1.44
~RD: IC8.2, S1.32
~ROMEN: IC4.20 (~CE), S1.42
~ROMOE: IC4.22 (~OE), IC5.2

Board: 2 copper layers, 60 parts (0 on the bottom side), 101 nets, no tracks yet.

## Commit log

2022-07-14 First version passing ERC
2022-07-14 Slightly rearrange to fit on smaller paper
2022-07-14 Start placing components
2022-07-14 PCB work
2022-07-17 ROMless variant schematic, CPC Dandanator CPLD
2022-07-17 CPLD constraint file for CPC Dandanator
2022-07-31 routed no-rom board
2022-08-01 Silkscreen work
2022-08-01 3D renderings of v0.1
2022-08-01 Unround corners
2022-08-03 Begin CPLD work
2022-08-03 Fixup Makefile
2022-08-03 xst file + makefile updates
2022-08-03 More XST work
2022-08-03 CPLD top level and constraints
2022-08-03 CPLD version PCB
2022-08-03 Fix VHDL errors
2022-08-03 First cut at implementing CPLD logic
2022-08-03 Clock nFDCCS on rising edge
2022-08-03 add .jed file
2022-08-04 Version with ROM
2022-08-04 tweaks
2022-08-07 Layout with ROM redone
2022-08-07 VHDL and constraints update
2022-08-09 sent TTL variant to aisler for production
2022-08-09 Update version number
2022-12-03 reorganize and fix no-rom pcb and schematic
2022-12-03 Add README.md
2022-12-03 re-fill zones
2022-12-12 Save work
2023-01-04 Save CPLD work
2024-04-09 v1.0 sent to jlcpcb for production
2024-04-11 add new vhdl code
2024-04-11 xc9572xl 3d model
2024-04-12 cpl wip
2024-04-17 first attempt with cpld
2024-04-17 save wip
2024-06-02 make mtron_n be open drain active 0
2024-06-03 assign address selection to pin
2024-06-03 add address select jumper to schematics
